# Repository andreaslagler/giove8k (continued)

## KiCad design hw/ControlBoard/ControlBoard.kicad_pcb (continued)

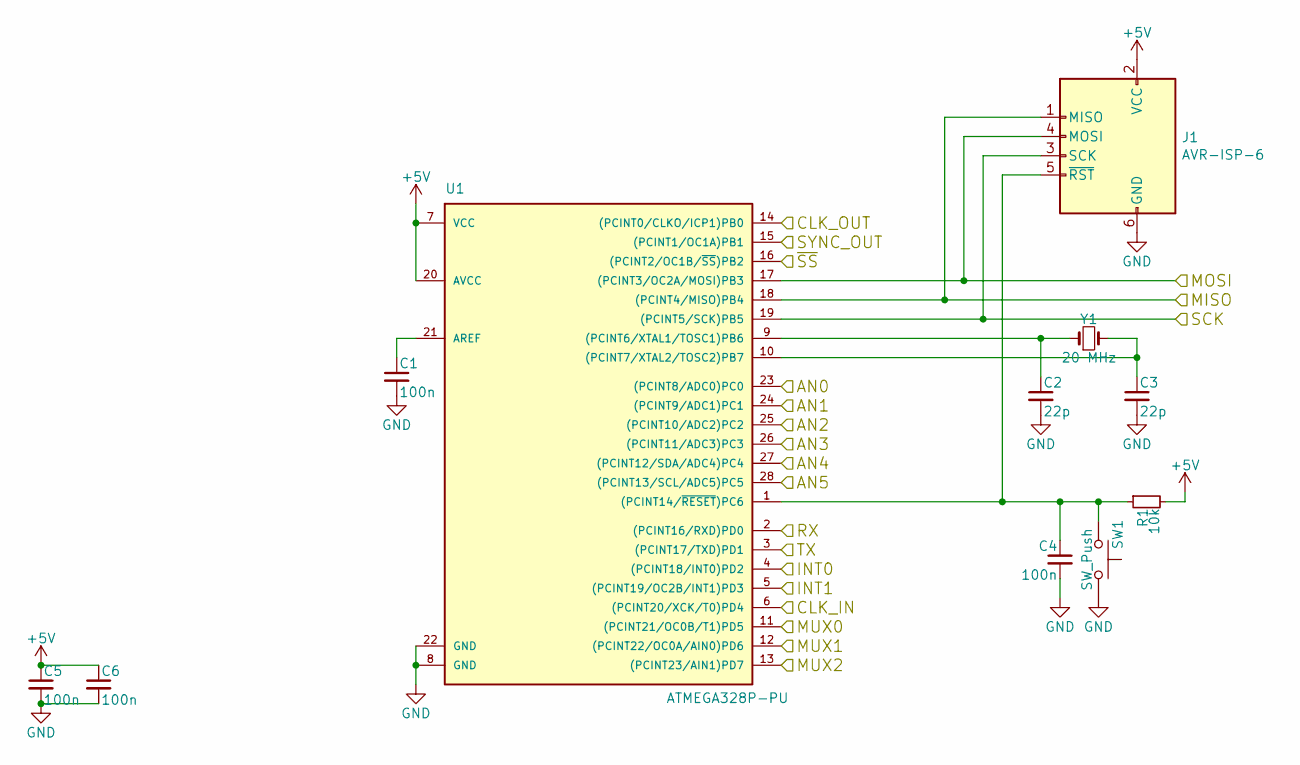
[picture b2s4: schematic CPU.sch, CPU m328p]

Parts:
C1, C4, C5, C6: 100n; C_Disc_D5.0mm_W2.5mm_P5.00mm
C2, C3: 22p; C_Disc_D3.0mm_W1.6mm_P2.50mm
J1: AVR-ISP-6; IDC-Header_2x03_P2.54mm_Vertical
R1: 10k; R_Axial_DIN0207_L6.3mm_D2.5mm_P10.16mm_Horizontal
SW1: SW_Push; SW_PUSH_6mm
U1: ATMEGA328P-PU; DIP-28_W7.62mm
Y1: 20 MHz; Crystal_HC49-U_Vertical

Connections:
+5V: C5.1, C6.1, J1.2 (VCC), R1.2, U1.7 (VCC), U1.20 (AVCC); also elsewhere on the board
/Controller/AN0: U1.23 ((PCINT8/ADC0)PC0); also elsewhere on the board
/Controller/AN1: U1.24 ((PCINT9/ADC1)PC1); also elsewhere on the board
/Controller/AN2: U1.25 ((PCINT10/ADC2)PC2); also elsewhere on the board
/Controller/AN3: U1.26 ((PCINT11/ADC3)PC3); also elsewhere on the board
/Controller/AN4: U1.27 ((PCINT12/SDA/ADC4)PC4); also elsewhere on the board
/Controller/CLK_IN: U1.6 ((PCINT20/XCK/T0)PD4); also elsewhere on the board
/Controller/CLK_OUT: U1.14 ((PCINT0/CLKO/ICP1)PB0); also elsewhere on the board
/Controller/INT0: U1.4 ((PCINT18/INT0)PD2); also elsewhere on the board
/Controller/INT1: U1.5 ((PCINT19/OC2B/INT1)PD3); also elsewhere on the board
/Controller/MUX0: U1.11 ((PCINT21/OC0B/T1)PD5); also elsewhere on the board
/Controller/MUX1: U1.12 ((PCINT22/OC0A/AIN0)PD6); also elsewhere on the board
/Controller/MUX2: U1.13 ((PCINT23/AIN1)PD7); also elsewhere on the board
/Controller/Rx: U1.2 ((PCINT16/RXD)PD0); also elsewhere on the board
/Controller/SCK: J1.3 (SCK), U1.19 ((PCINT5/SCK)PB5); also elsewhere on the board
/Controller/SDI: J1.1 (MISO), U1.18 ((PCINT4/MISO)PB4); also elsewhere on the board
/Controller/SDO: J1.4 (MOSI), U1.17 ((PCINT3/OC2A/MOSI)PB3); also elsewhere on the board
/Controller/SYNC_OUT: U1.15 ((PCINT1/OC1A)PB1); also elsewhere on the board
/Controller/Tx: U1.3 ((PCINT17/TXD)PD1); also elsewhere on the board
/Controller/~SS: U1.16 ((PCINT2/OC1B/~SS~)PB2); also elsewhere on the board
GND: C1.2, C2.2, C3.2, C4.2, C5.2, C6.2, J1.6 (GND), SW1.1, U1.8 (GND), U1.22 (GND); also elsewhere on the board
unnamed: C1.1, U1.21 (AREF)
unnamed: C2.1, U1.9 ((PCINT6/XTAL1/TOSC1)PB6), Y1.1
unnamed: C3.1, U1.10 ((PCINT7/XTAL2/TOSC2)PB7), Y1.2
unnamed: C4.1, J1.5 (~RST), R1.1, SW1.2, U1.1 ((PCINT14/~RESET~)PC6)

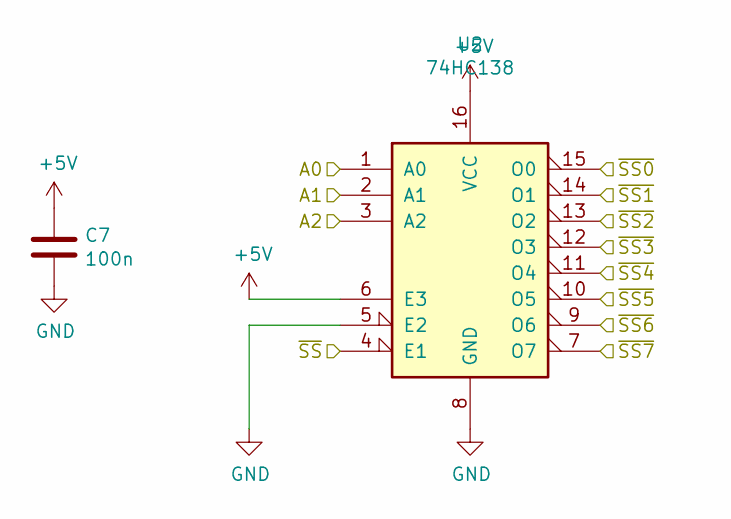
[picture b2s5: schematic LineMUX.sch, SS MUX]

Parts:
C7: 100n; C_Disc_D5.0mm_W2.5mm_P5.00mm
U2: 74HC138; DIP-16_W7.62mm

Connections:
+5V: C7.1, U2.6 (E3), U2.16 (VCC); also elsewhere on the board
/Controller/MUX0: U2.1 (A0); also elsewhere on the board
/Controller/MUX1: U2.2 (A1); also elsewhere on the board
/Controller/MUX2: U2.3 (A2); also elsewhere on the board
/Controller/~SS: U2.4 (E1); also elsewhere on the board
/Controller/~SS0: U2.15 (O0); also elsewhere on the board
/Controller/~SS1: U2.14 (O1); also elsewhere on the board
/Controller/~SS3: U2.12 (O3); also elsewhere on the board
/Controller/~SS4: U2.11 (O4); also elsewhere on the board
/Controller/~SS5: U2.10 (O5); also elsewhere on the board
/Controller/~SS6: U2.9 (O6); also elsewhere on the board
/Controller/~SS7: U2.7 (O7); also elsewhere on the board
/Controller/~SSDSP: U2.13 (O2); also elsewhere on the board
GND: C7.2, U2.5 (E2), U2.8 (GND); also elsewhere on the board

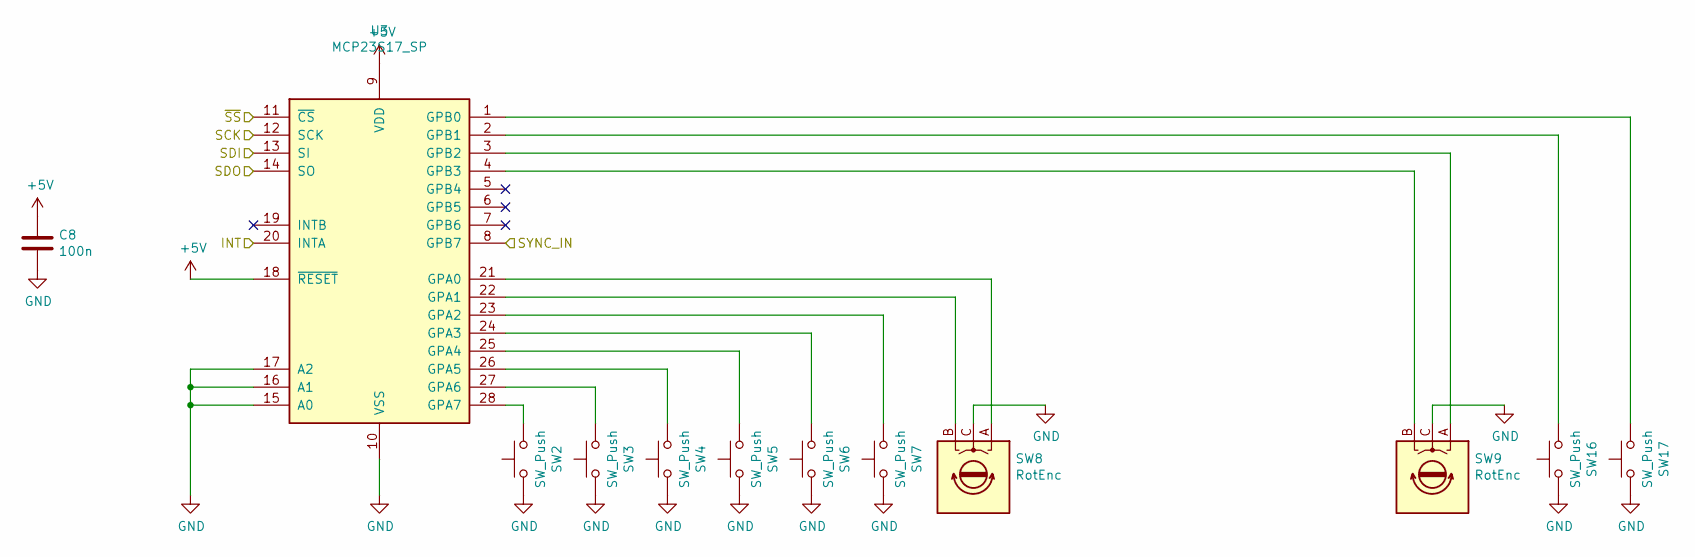
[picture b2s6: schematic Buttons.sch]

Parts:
C8: 100n; C_Disc_D5.0mm_W2.5mm_P5.00mm
SW2, SW3, SW4, SW5, SW6, SW7, SW16, SW17: SW_Push; SW_PUSH-12mm
SW8, SW9: RotEnc; RotaryEncoder_Alps_EC12E_Vertical_H20mm_CircularMountingHol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
U3: MCP23S17_SP; DIP-28_W7.62mm

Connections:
+5V: C8.1, U3.9 (VDD), U3.18 (~RESET~); also elsewhere on the board
/Controller/INT1: U3.20 (INTA); also elsewhere on the board
/Controller/SCK: U3.12 (SCK); also elsewhere on the board
/Controller/SDI: U3.14 (SO); also elsewhere on the board
/Controller/SDO: U3.13 (SI); also elsewhere on the board
/Controller/SYNC_IN: U3.8 (GPB7); also elsewhere on the board
/Controller/~SS1: U3.11 (~CS~); also elsewhere on the board
GND: C8.2, SW2.1, SW3.1, SW4.1, SW5.1, SW6.1, SW7.1, SW8.C, SW9.C, SW16.1, SW17.1, U3.10 (VSS), U3.15 (A0), U3.16 (A1), U3.17 (A2); also elsewhere on the board
unnamed: SW2.2, U3.28 (GPA7)
unnamed: SW3.2, U3.27 (GPA6)
unnamed: SW4.2, U3.26 (GPA5)
unnamed: SW5.2, U3.25 (GPA4)
unnamed: SW6.2, U3.24 (GPA3)
unnamed: SW7.2, U3.23 (GPA2)
unnamed: SW8.A, U3.21 (GPA0)
unnamed: SW8.B, U3.22 (GPA1)
unnamed: SW9.A, U3.3 (GPB2)
unnamed: SW9.B, U3.4 (GPB3)
unnamed: SW16.2, U3.2 (GPB1)
unnamed: SW17.2, U3.1 (GPB0)

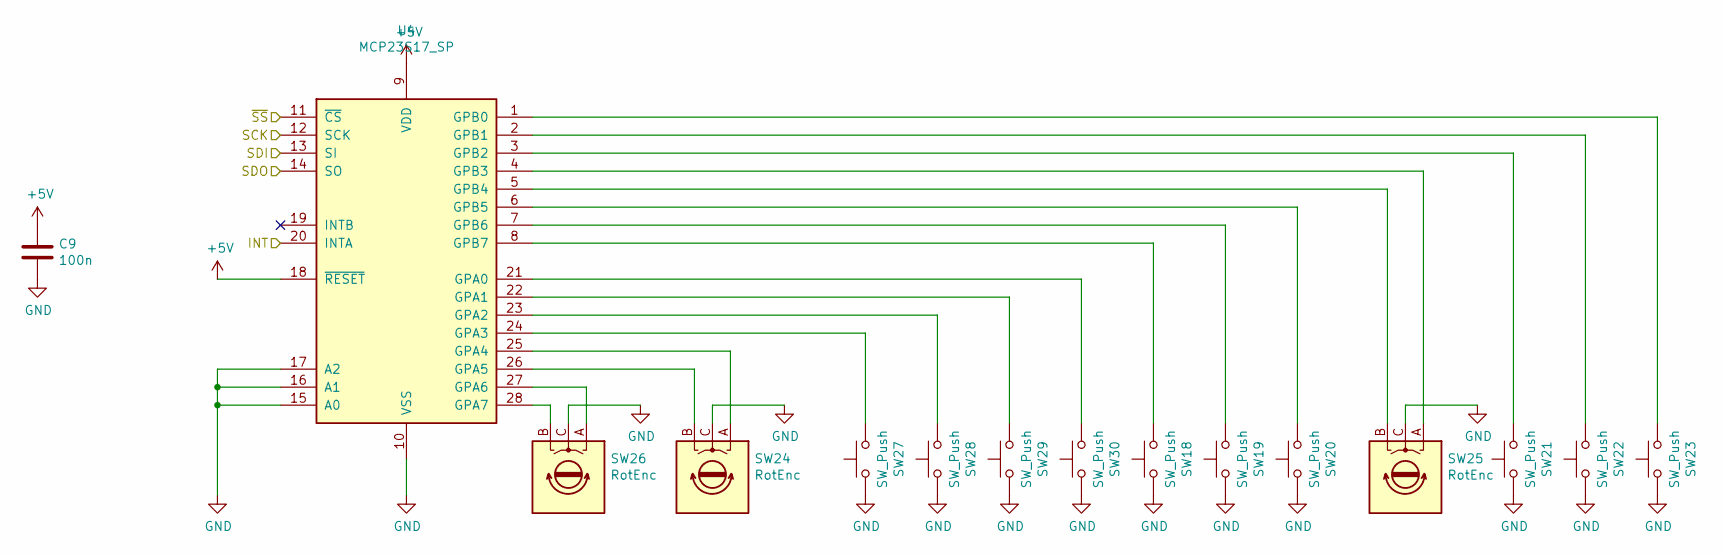
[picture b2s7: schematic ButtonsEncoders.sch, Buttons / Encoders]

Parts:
C9: 100n; C_Disc_D5.0mm_W2.5mm_P5.00mm
SW18, SW19, SW20, SW21, SW22, SW23, SW27, SW28, SW29, SW30: SW_Push; SW_PUSH-12mm
SW24, SW25, SW26: RotEnc; RotaryEncoder_Alps_EC12E_Vertical_H20mm_CircularMountingHol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
U4: MCP23S17_SP; DIP-28_W7.62mm

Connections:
+5V: C9.1, U4.9 (VDD), U4.18 (~RESET~); also elsewhere on the board
/Controller/INT0: U4.20 (INTA); also elsewhere on the board
/Controller/SCK: U4.12 (SCK); also elsewhere on the board
/Controller/SDI: U4.14 (SO); also elsewhere on the board
/Controller/SDO: U4.13 (SI); also elsewhere on the board
/Controller/~SS7: U4.11 (~CS~); also elsewhere on the board
GND: C9.2, SW18.1, SW19.1, SW20.1, SW21.1, SW22.1, SW23.1, SW24.C, SW25.C, SW26.C, SW27.1, SW28.1, SW29.1, SW30.1, U4.10 (VSS), U4.15 (A0), U4.16 (A1), U4.17 (A2); also elsewhere on the board
unnamed: SW18.2, U4.8 (GPB7)
unnamed: SW19.2, U4.7 (GPB6)
unnamed: SW20.2, U4.6 (GPB5)
unnamed: SW21.2, U4.3 (GPB2)
unnamed: SW22.2, U4.2 (GPB1)
unnamed: SW23.2, U4.1 (GPB0)
unnamed: SW24.A, U4.25 (GPA4)
unnamed: SW24.B, U4.26 (GPA5)
unnamed: SW25.A, U4.4 (GPB3)
unnamed: SW25.B, U4.5 (GPB4)
unnamed: SW26.A, U4.27 (GPA6)
unnamed: SW26.B, U4.28 (GPA7)
unnamed: SW27.2, U4.24 (GPA3)
unnamed: SW28.2, U4.23 (GPA2)
unnamed: SW29.2, U4.22 (GPA1)
unnamed: SW30.2, U4.21 (GPA0)

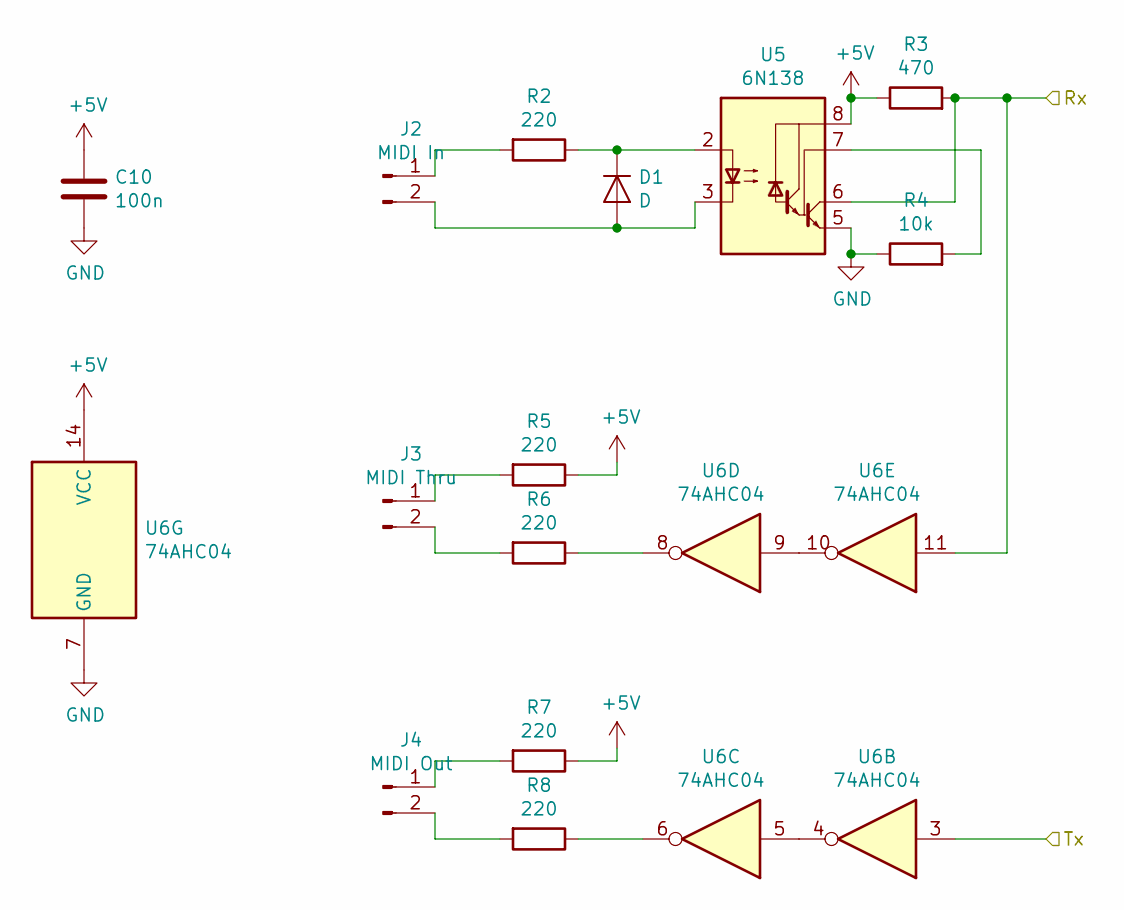
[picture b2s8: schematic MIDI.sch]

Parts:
C10: 100n; C_Disc_D5.0mm_W2.5mm_P5.00mm
D1: D; D_A-405_P10.16mm_Horizontal
J2: MIDI In; Molex_KK-254_AE-6410-02A_1x02_P2.54mm_Vertical
J3: MIDI Thru; Molex_KK-254_AE-6410-02A_1x02_P2.54mm_Vertical
J4: MIDI Out; Molex_KK-254_AE-6410-02A_1x02_P2.54mm_Vertical
R2, R5, R6, R7, R8: 220; R_Axial_DIN0207_L6.3mm_D2.5mm_P10.16mm_Horizontal
R3: 470; R_Axial_DIN0207_L6.3mm_D2.5mm_P10.16mm_Horizontal
R4: 10k; R_Axial_DIN0207_L6.3mm_D2.5mm_P10.16mm_Horizontal
U5: 6N138; DIP-8_W7.62mm
U6: 74AHC04; DIP-14_W7.62mm

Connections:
+5V: C10.1, R3.1, R5.1, R7.1, U5.8 (VCC), U6.14 (VCC); also elsewhere on the board
/Controller/Rx: R3.2, U5.6 (VO2), U6.11; also elsewhere on the board
/Controller/Tx: U6.3; also elsewhere on the board
GND: C10.2, R4.1, U5.5 (GND), U6.7 (GND); also elsewhere on the board
unnamed: D1.1 (K), R2.1, U5.2 (C1)
unnamed: D1.2 (A), J2.2, U5.3 (C2)
unnamed: J2.1, R2.2
unnamed: J3.1, R5.2
unnamed: J3.2, R6.2
unnamed: J4.1, R7.2
unnamed: J4.2, R8.2
unnamed: R4.2, U5.7 (VO1)
unnamed: R6.1, U6.8
unnamed: R8.1, U6.6
unnamed: U6.4, U6.5
unnamed: U6.9, U6.10

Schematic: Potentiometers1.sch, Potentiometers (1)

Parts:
C11: 100n; C_Disc_D5.0mm_W2.5mm_P5.00mm
RV1, RV2, RV3, RV4, RV5, RV6, RV7, RV8: 10kB; Potentiometer_Alpha_RD901F-40-00D_Single_Vertical_CircularH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
U7: 4051; DIP-16_W7.62mm

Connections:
+5V: C11.1, RV1.3, RV2.3, RV3.3, RV4.3, RV5.3, RV6.3, RV7.3, RV8.3, U7.16 (VDD); also elsewhere on the board
/Controller/AN2: U7.3 (X); also elsewhere on the board
/Controller/MUX0: U7.11 (A); also elsewhere on the board
/Controller/MUX1: U7.10 (B); also elsewhere on the board
/Controller/MUX2: U7.9 (C); also elsewhere on the board
GND: C11.2, RV1.1, RV2.1, RV3.1, RV4.1, RV5.1, RV6.1, RV7.1, RV8.1, U7.6 (Inh), U7.7 (VEE), U7.8 (VSS); also elsewhere on the board
unnamed: RV1.2, U7.4 (X7)
unnamed: RV2.2, U7.2 (X6)
unnamed: RV3.2, U7.5 (X5)
unnamed: RV4.2, U7.1 (X4)
unnamed: RV5.2, U7.12 (X3)
unnamed: RV6.2, U7.15 (X2)
unnamed: RV7.2, U7.14 (X1)
unnamed: RV8.2, U7.13 (X0)

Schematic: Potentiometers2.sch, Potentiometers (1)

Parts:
C12: 100n; C_Disc_D5.0mm_W2.5mm_P5.00mm
RV9, RV10, RV11, RV12, RV13, RV14, RV15, RV16: 10kB; Potentiometer_Alpha_RD901F-40-00D_Single_Vertical_CircularH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
U8: 4051; DIP-16_W7.62mm

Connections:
+5V: C12.1, RV9.3, RV10.3, RV11.3, RV12.3, RV13.3, RV14.3, RV15.3, RV16.3, U8.16 (VDD); also elsewhere on the board
/Controller/AN0: U8.3 (X); also elsewhere on the board
/Controller/MUX0: U8.11 (A); also elsewhere on the board
/Controller/MUX1: U8.10 (B); also elsewhere on the board
/Controller/MUX2: U8.9 (C); also elsewhere on the board
GND: C12.2, RV9.1, RV10.1, RV11.1, RV12.1, RV13.1, RV14.1, RV15.1, RV16.1, U8.6 (Inh), U8.7 (VEE), U8.8 (VSS); also elsewhere on the board
unnamed: RV9.2, U8.4 (X7)
unnamed: RV10.2, U8.2 (X6)
unnamed: RV11.2, U8.5 (X5)
unnamed: RV12.2, U8.1 (X4)
unnamed: RV13.2, U8.12 (X3)
unnamed: RV14.2, U8.15 (X2)
unnamed: RV15.2, U8.14 (X1)
unnamed: RV16.2, U8.13 (X0)

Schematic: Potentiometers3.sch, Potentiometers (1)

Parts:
C13: 100n; C_Disc_D5.0mm_W2.5mm_P5.00mm
RV17, RV18, RV19, RV20, RV21, RV22, RV23, RV24: 10kB; Potentiometer_Alpha_RD901F-40-00D_Single_Vertical_CircularH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
U9: 4051; DIP-16_W7.62mm

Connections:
+5V: C13.1, RV17.3, RV18.3, RV19.3, RV20.3, RV21.3, RV22.3, RV23.3, RV24.3, U9.16 (VDD); also elsewhere on the board
/Controller/AN4: U9.3 (X); also elsewhere on the board
/Controller/MUX0: U9.11 (A); also elsewhere on the board
/Controller/MUX1: U9.10 (B); also elsewhere on the board
/Controller/MUX2: U9.9 (C); also elsewhere on the board
GND: C13.2, RV17.1, RV18.1, RV19.1, RV20.1, RV21.1, RV22.1, RV23.1, RV24.1, U9.6 (Inh), U9.7 (VEE), U9.8 (VSS); also elsewhere on the board
unnamed: RV17.2, U9.4 (X7)
unnamed: RV18.2, U9.2 (X6)
unnamed: RV19.2, U9.5 (X5)
unnamed: RV20.2, U9.1 (X4)
unnamed: RV21.2, U9.12 (X3)
unnamed: RV22.2, U9.15 (X2)
unnamed: RV23.2, U9.14 (X1)
unnamed: RV24.2, U9.13 (X0)

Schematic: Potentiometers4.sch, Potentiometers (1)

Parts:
C14: 100n; C_Disc_D5.0mm_W2.5mm_P5.00mm
RV25, RV26, RV27, RV28, RV30, RV31, RV32: 10kB; Potentiometer_Alpha_RD901F-40-00D_Single_Vertical_CircularH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
U10: 4051; DIP-16_W7.62mm

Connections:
+5V: C14.1, RV25.3, RV26.3, RV27.3, RV28.3, RV30.3, RV31.3, RV32.3, U10.16 (VDD); also elsewhere on the board
/Controller/AN3: U10.3 (X); also elsewhere on the board
/Controller/MUX0: U10.11 (A); also elsewhere on the board
/Controller/MUX1: U10.10 (B); also elsewhere on the board
/Controller/MUX2: U10.9 (C); also elsewhere on the board
GND: C14.2, RV25.1, RV26.1, RV27.1, RV28.1, RV30.1, RV31.1, RV32.1, U10.6 (Inh), U10.7 (VEE), U10.8 (VSS); also elsewhere on the board
unnamed: RV25.2, U10.4 (X7)
unnamed: RV26.2, U10.2 (X6)
unnamed: RV27.2, U10.5 (X5)
unnamed: RV28.2, U10.1 (X4)
unnamed: RV30.2, U10.15 (X2)
unnamed: RV31.2, U10.14 (X1)
unnamed: RV32.2, U10.13 (X0)

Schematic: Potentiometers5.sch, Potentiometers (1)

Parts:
C15: 100n; C_Disc_D5.0mm_W2.5mm_P5.00mm
RV33, RV34, RV35, RV36, RV37, RV40, RV42: 10kB; Potentiometer_Alpha_RD901F-40-00D_Single_Vertical_CircularH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
U11: 4051; DIP-16_W7.62mm

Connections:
+5V: C15.1, RV33.3, RV34.3, RV35.3, RV36.3, RV37.3, RV40.3, RV42.3, U11.16 (VDD); also elsewhere on the board
/Controller/AN1: U11.3 (X); also elsewhere on the board
/Controller/MUX0: U11.11 (A); also elsewhere on the board
/Controller/MUX1: U11.10 (B); also elsewhere on the board
/Controller/MUX2: U11.9 (C); also elsewhere on the board
GND: C15.2, RV33.1, RV34.1, RV35.1, RV36.1, RV37.1, RV40.1, RV42.1, U11.6 (Inh), U11.7 (VEE), U11.8 (VSS); also elsewhere on the board
unnamed: RV33.2, U11.4 (X7)
unnamed: RV34.2, U11.2 (X6)
unnamed: RV35.2, U11.5 (X5)
unnamed: RV36.2, U11.1 (X4)
unnamed: RV37.2, U11.12 (X3)
unnamed: RV40.2, U11.14 (X1)
unnamed: RV42.2, U11.13 (X0)

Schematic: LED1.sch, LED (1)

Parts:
C16: 100n; C_Disc_D5.0mm_W2.5mm_P5.00mm
D2, D3, D4, D5, D6, D7, D8, D9: LED; LED_D3.0mm
R9, R10, R11, R12, R13, R14, R15, R16: 1k5; R_Axial_DIN0207_L6.3mm_D2.5mm_P10.16mm_Horizontal
U12: 74HC595; DIP-16_W7.62mm

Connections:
+5V: C16.1, U12.10 (~SRCLR), U12.16 (VCC); also elsewhere on the board
/Controller/LED (1)/SDI: U12.14 (SER); also elsewhere on the board
/Controller/LED (3)/SDI: U12.9 (QH'); also elsewhere on the board
/Controller/SCK: U12.11 (SRCLK); also elsewhere on the board
/Controller/~SS0: U12.12 (RCLK); also elsewhere on the board
GND: C16.2, D2.1 (K), D3.1 (K), D4.1 (K), D5.1 (K), D6.1 (K), D7.1 (K), D8.1 (K), D9.1 (K), U12.8 (GND), U12.13 (~OE); also elsewhere on the board
unnamed: D2.2 (A), R9.2
unnamed: D3.2 (A), R10.2
unnamed: D4.2 (A), R11.2
unnamed: D5.2 (A), R12.2
unnamed: D6.2 (A), R13.2
unnamed: D7.2 (A), R14.2
unnamed: D8.2 (A), R15.2
unnamed: D9.2 (A), R16.2
unnamed: R9.1, U12.7 (QH)
unnamed: R10.1, U12.6 (QG)
unnamed: R11.1, U12.5 (QF)
unnamed: R12.1, U12.4 (QE)
unnamed: R13.1, U12.3 (QD)
unnamed: R14.1, U12.2 (QC)
unnamed: R15.1, U12.1 (QB)
unnamed: R16.1, U12.15 (QA)

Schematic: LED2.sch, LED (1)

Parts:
C17: 100n; C_Disc_D5.0mm_W2.5mm_P5.00mm
D10, D11, D12, D13, D14, D15: LED; LED_D3.0mm
R17, R18, R19, R20, R21, R22: 1k5; R_Axial_DIN0207_L6.3mm_D2.5mm_P10.16mm_Horizontal
U13: 74HC595; DIP-16_W7.62mm

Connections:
+5V: C17.1, U13.10 (~SRCLR), U13.16 (VCC); also elsewhere on the board
/Controller/LED (1)/SDI: U13.9 (QH'); also elsewhere on the board
/Controller/LED (2)/SDI: U13.14 (SER); also elsewhere on the board
/Controller/SCK: U13.11 (SRCLK); also elsewhere on the board
/Controller/~SS0: U13.12 (RCLK); also elsewhere on the board
GND: C17.2, D10.1 (K), D11.1 (K), D12.1 (K), D13.1 (K), D14.1 (K), D15.1 (K), U13.8 (GND), U13.13 (~OE); also elsewhere on the board
unnamed: D10.2 (A), R17.2
unnamed: D11.2 (A), R18.2
unnamed: D12.2 (A), R19.2
unnamed: D13.2 (A), R20.2
unnamed: D14.2 (A), R21.2
unnamed: D15.2 (A), R22.2
unnamed: R17.1, U13.7 (QH)
unnamed: R18.1, U13.6 (QG)
unnamed: R19.1, U13.5 (QF)
unnamed: R20.1, U13.4 (QE)
unnamed: R21.1, U13.3 (QD)
unnamed: R22.1, U13.2 (QC)

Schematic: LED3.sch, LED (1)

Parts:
C18: 100n; C_Disc_D5.0mm_W2.5mm_P5.00mm
D18, D19, D20, D21, D22, D23, D24, D25: LED; LED_D3.0mm
R25, R26, R27, R28, R29, R30, R31, R32: 1k5; R_Axial_DIN0207_L6.3mm_D2.5mm_P10.16mm_Horizontal
U14: 74HC595; DIP-16_W7.62mm

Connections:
+5V: C18.1, U14.10 (~SRCLR), U14.16 (VCC); also elsewhere on the board
/Controller/LED (3)/SDI: U14.14 (SER); also elsewhere on the board
/Controller/SCK: U14.11 (SRCLK); also elsewhere on the board
/Controller/~SS0: U14.12 (RCLK); also elsewhere on the board
GND: C18.2, D18.1 (K), D19.1 (K), D20.1 (K), D21.1 (K), D22.1 (K), D23.1 (K), D24.1 (K), D25.1 (K), U14.8 (GND), U14.13 (~OE); also elsewhere on the board
unnamed: D18.2 (A), R25.2
unnamed: D19.2 (A), R26.2
unnamed: D20.2 (A), R27.2
unnamed: D21.2 (A), R28.2
unnamed: D22.2 (A), R29.2
unnamed: D23.2 (A), R30.2
unnamed: D24.2 (A), R31.2
unnamed: D25.2 (A), R32.2
unnamed: R25.1, U14.7 (QH)
unnamed: R26.1, U14.6 (QG)
unnamed: R27.1, U14.5 (QF)
unnamed: R28.1, U14.4 (QE)
unnamed: R29.1, U14.3 (QD)
unnamed: R30.1, U14.2 (QC)
unnamed: R31.1, U14.1 (QB)
unnamed: R32.1, U14.15 (QA)

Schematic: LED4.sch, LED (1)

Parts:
C19: 100n; C_Disc_D5.0mm_W2.5mm_P5.00mm
D26, D27, D28, D29, D30, D31, D32, D33: LED; LED_D3.0mm
R33, R34, R35, R36, R37, R38, R39, R40: 1k5; R_Axial_DIN0207_L6.3mm_D2.5mm_P10.16mm_Horizontal
U15: 74HC595; DIP-16_W7.62mm

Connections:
+5V: C19.1, U15.10 (~SRCLR), U15.16 (VCC); also elsewhere on the board
/Controller/LED (2)/SDI: U15.9 (QH'); also elsewhere on the board
/Controller/LED (4)/SDI: U15.14 (SER); also elsewhere on the board
/Controller/SCK: U15.11 (SRCLK); also elsewhere on the board
/Controller/~SS0: U15.12 (RCLK); also elsewhere on the board
GND: C19.2, D26.1 (K), D27.1 (K), D28.1 (K), D29.1 (K), D30.1 (K), D31.1 (K), D32.1 (K), D33.1 (K), U15.8 (GND), U15.13 (~OE); also elsewhere on the board
unnamed: D26.2 (A), R33.2
unnamed: D27.2 (A), R34.2
unnamed: D28.2 (A), R35.2
unnamed: D29.2 (A), R36.2
unnamed: D30.2 (A), R37.2
unnamed: D31.2 (A), R38.2
unnamed: D32.2 (A), R39.2
unnamed: D33.2 (A), R40.2
unnamed: R33.1, U15.7 (QH)
unnamed: R34.1, U15.6 (QG)
unnamed: R35.1, U15.5 (QF)
unnamed: R36.1, U15.4 (QE)
unnamed: R37.1, U15.3 (QD)
unnamed: R38.1, U15.2 (QC)
unnamed: R39.1, U15.1 (QB)
unnamed: R40.1, U15.15 (QA)

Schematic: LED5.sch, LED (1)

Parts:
C20: 100n; C_Disc_D5.0mm_W2.5mm_P5.00mm
D34, D35, D36, D37, D38, D39, D40, D41: LED; LED_D3.0mm
R41, R42, R43, R44, R45, R46, R47, R48: 1k5; R_Axial_DIN0207_L6.3mm_D2.5mm_P10.16mm_Horizontal
U16: 74HC595; DIP-16_W7.62mm

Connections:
+5V: C20.1, U16.10 (~SRCLR), U16.16 (VCC); also elsewhere on the board
/Controller/LED (4)/SDI: U16.9 (QH'); also elsewhere on the board
/Controller/LED (5)/SDI: U16.14 (SER); also elsewhere on the board
/Controller/SCK: U16.11 (SRCLK); also elsewhere on the board
/Controller/~SS0: U16.12 (RCLK); also elsewhere on the board
GND: C20.2, D34.1 (K), D35.1 (K), D36.1 (K), D37.1 (K), D38.1 (K), D39.1 (K), D40.1 (K), D41.1 (K), U16.8 (GND), U16.13 (~OE); also elsewhere on the board
unnamed: D34.2 (A), R41.2
unnamed: D35.2 (A), R42.2
unnamed: D36.2 (A), R43.2
unnamed: D37.2 (A), R44.2
unnamed: D38.2 (A), R45.2
unnamed: D39.2 (A), R46.2
unnamed: D40.2 (A), R47.2
unnamed: D41.2 (A), R48.2
unnamed: R41.1, U16.7 (QH)
unnamed: R42.1, U16.6 (QG)
unnamed: R43.1, U16.5 (QF)
unnamed: R44.1, U16.4 (QE)
unnamed: R45.1, U16.3 (QD)
unnamed: R46.1, U16.2 (QC)
unnamed: R47.1, U16.1 (QB)
unnamed: R48.1, U16.15 (QA)

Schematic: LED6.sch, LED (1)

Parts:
C21: 100n; C_Disc_D5.0mm_W2.5mm_P5.00mm
D42, D43, D44, D45, D46, D47, D48, D49: LED; LED_D3.0mm
R49, R50, R51, R52, R53, R54, R55, R56: 1k5; R_Axial_DIN0207_L6.3mm_D2.5mm_P10.16mm_Horizontal
U17: 74HC595; DIP-16_W7.62mm

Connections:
+5V: C21.1, U17.10 (~SRCLR), U17.16 (VCC); also elsewhere on the board
/Controller/LED (5)/SDI: U17.9 (QH'); also elsewhere on the board
/Controller/SCK: U17.11 (SRCLK); also elsewhere on the board
/Controller/SDO: U17.14 (SER); also elsewhere on the board
/Controller/~SS0: U17.12 (RCLK); also elsewhere on the board
GND: C21.2, D42.1 (K), D43.1 (K), D44.1 (K), D45.1 (K), D46.1 (K), D47.1 (K), D48.1 (K), D49.1 (K), U17.8 (GND), U17.13 (~OE); also elsewhere on the board
unnamed: D42.2 (A), R49.2
unnamed: D43.2 (A), R50.2
unnamed: D44.2 (A), R51.2
unnamed: D45.2 (A), R52.2
unnamed: D46.2 (A), R53.2
unnamed: D47.2 (A), R54.2
unnamed: D48.2 (A), R55.2
unnamed: D49.2 (A), R56.2
unnamed: R49.1, U17.7 (QH)
unnamed: R50.1, U17.6 (QG)
unnamed: R51.1, U17.5 (QF)
unnamed: R52.1, U17.4 (QE)
unnamed: R53.1, U17.3 (QD)
unnamed: R54.1, U17.2 (QC)
unnamed: R55.1, U17.1 (QB)
unnamed: R56.1, U17.15 (QA)

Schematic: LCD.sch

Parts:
C22: 100n; C_Disc_D5.0mm_W2.5mm_P5.00mm
DS1: WC1602A
Q1: 2N3904; TO-92
R57: 10k; R_Axial_DIN0207_L6.3mm_D2.5mm_P10.16mm_Horizontal
R58: 100k; R_Axial_DIN0207_L6.3mm_D2.5mm_P10.16mm_Horizontal
R59: 100; R_Axial_DIN0207_L6.3mm_D2.5mm_P10.16mm_Horizontal
RV41: 10k; Potentiometer_Piher_PT-6-V_Vertical
U18: 74HC595; DIP-16_W7.62mm

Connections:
+5V: C22.1, DS1.2 (VDD), DS1.15 (LED(+)), R57.1, RV41.3, U18.10 (~SRCLR), U18.16 (VCC); also elsewhere on the board
/Controller/SCK: U18.11 (SRCLK); also elsewhere on the board
/Controller/SDO: U18.14 (SER); also elsewhere on the board
/Controller/~SS3: R58.2, U18.12 (RCLK); also elsewhere on the board
GND: C22.2, DS1.1 (VSS), DS1.5 (R/W), Q1.1 (E), R59.2, RV41.1, U18.8 (GND), U18.13 (~OE); also elsewhere on the board
unnamed: DS1.3 (VO), RV41.2
unnamed: DS1.4 (RS), U18.2 (QC)
unnamed: DS1.6 (E), Q1.3 (C), R57.2
unnamed: DS1.11 (D4), U18.4 (QE)
unnamed: DS1.12 (D5), U18.5 (QF)
unnamed: DS1.13 (D6), U18.6 (QG)
unnamed: DS1.14 (D7), U18.7 (QH)
unnamed: DS1.16 (LED(-)), R59.1
unnamed: Q1.2 (B), R58.1

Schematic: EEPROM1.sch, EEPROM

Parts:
C23: 100n; C_Disc_D5.0mm_W2.5mm_P5.00mm
U19: 25LC512; DIP-8_W7.62mm

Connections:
+5V: C23.1, U19.3 (~WP), U19.7 (~HOLD), U19.8 (VCC); also elsewhere on the board
/Controller/SCK: U19.6 (SCK); also elsewhere on the board
/Controller/SDI: U19.2 (MISO); also elsewhere on the board
/Controller/SDO: U19.5 (MOSI); also elsewhere on the board
/Controller/~SS4: U19.1 (~CS); also elsewhere on the board
GND: C23.2, U19.4 (GND); also elsewhere on the board

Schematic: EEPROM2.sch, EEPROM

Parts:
C28: 100n; C_Disc_D5.0mm_W2.5mm_P5.00mm
U22: 25LC512; DIP-8_W7.62mm

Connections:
+5V: C28.1, U22.3 (~WP), U22.7 (~HOLD), U22.8 (VCC); also elsewhere on the board
/Controller/SCK: U22.6 (SCK); also elsewhere on the board
/Controller/SDI: U22.2 (MISO); also elsewhere on the board
/Controller/SDO: U22.5 (MOSI); also elsewhere on the board
/Controller/~SS5: U22.1 (~CS); also elsewhere on the board
GND: C28.2, U22.4 (GND); also elsewhere on the board

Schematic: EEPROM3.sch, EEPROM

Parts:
C29: 100n; C_Disc_D5.0mm_W2.5mm_P5.00mm
U23: 25LC512; DIP-8_W7.62mm

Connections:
+5V: C29.1, U23.3 (~WP), U23.7 (~HOLD), U23.8 (VCC); also elsewhere on the board
/Controller/SCK: U23.6 (SCK); also elsewhere on the board
/Controller/SDI: U23.2 (MISO); also elsewhere on the board
/Controller/SDO: U23.5 (MOSI); also elsewhere on the board
/Controller/~SS6: U23.1 (~CS); also elsewhere on the board
GND: C29.2, U23.4 (GND); also elsewhere on the board

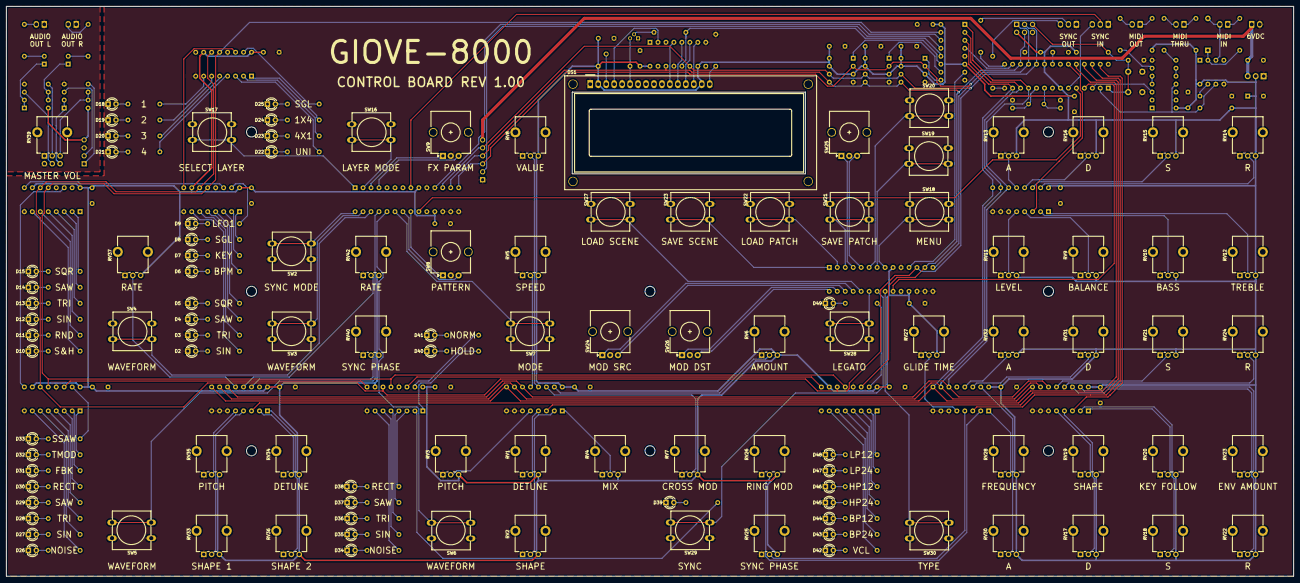
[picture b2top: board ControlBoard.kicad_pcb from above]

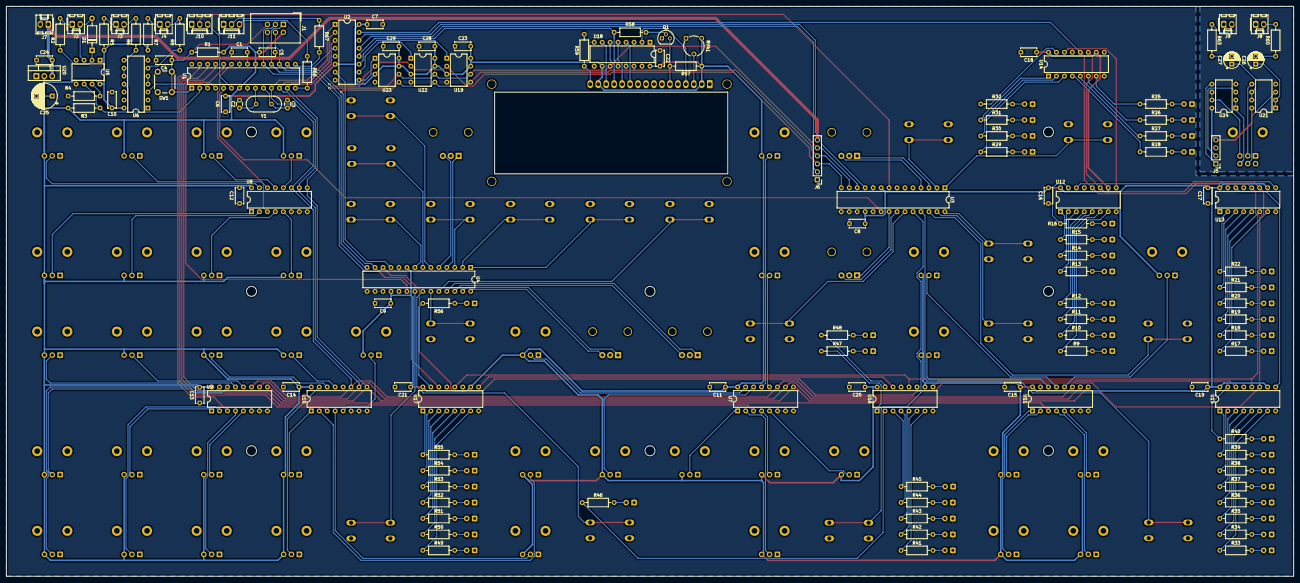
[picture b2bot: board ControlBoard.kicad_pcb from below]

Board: 2 copper layers, 410.2 x 181.6 mm, 239 parts (130 on the bottom side), 235 nets.

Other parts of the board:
J7: 6VDC; Molex_KK-254_AE-6410-02A_1x02_P2.54mm_Vertical

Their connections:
+6V: J7.1; also elsewhere on the board
GND: J7.2; also elsewhere on the board

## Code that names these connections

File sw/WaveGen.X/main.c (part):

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
// FOSC
#pragma config POSCMD = XT              // Primary Oscillator Mode Select bits (XT Crystal Oscillator Mode)
#pragma config OSCIOFNC = OFF           // OSC2 Pin Function bit (OSC2 is clock output)
#pragma config IOL1WAY = ON             // Peripheral pin select configuration (Allow only one reconfiguration)
#pragma config FCKSM = CSECMD           // Clock Switching Mode bits (Clock switching is enabled,Fail-safe Clock Monitor is disabled)

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    ////////////////////////////////////////////////////////////////////////////
    // SPI1 is configured as master with two /SS pins for external SRAM control

    // SCK1 -> Pin 16 - RB7
    TRISBbits.TRISB7 = 0;
    LATBbits.LATB7 = 0;

    // SDO1 -> Pin 17 - RB8
    TRISBbits.TRISB8 = 0;
    LATBbits.LATB8 = 0;

    // SDI1 -> Pin 18 - RB9
    TRISBbits.TRISB9 = 1;
    PORTBbits.RB9 = 0;

    // /SS10 -> Pin 15 - RB6
    TRISBbits.TRISB6 = 0;
    LATBbits.LATB6 = 1;

    // /SS11 -> Pin 22 - RB11
    TRISBbits.TRISB11 = 0;
    LATBbits.LATB11 = 1;

    ////////////////////////////////////////////////////////////////////////////
    // SPI2 is configured as slave

    // /SS2 --> Pin 23 - RB12 / RPI44 (input)
    TRISBbits.TRISB12 = 1;
    RPINR23bits.SS2R = 44;
 
    // SDI2 --> Pin 24 - RB13 / RPI45 (input)
    TRISBbits.TRISB13 = 1;
    RPINR22bits.SDI2R = 45;
 
    // SDO2 --> Pin 25 - RB14 / RPI46 (output) WIRING ERROR
    TRISBbits.TRISB14 = 1;
 
    // SDO2 --> Pin 21 - RB10 / RP42 (output)
    TRISBbits.TRISB10 = 0;
    LATBbits.LATB10 = 0;
    RPOR4bits.RP42R = 0b001000; // SDO2

    // SCK2 --> Pin 26 - RB15 / RPI47 (input)
    TRISBbits.TRISB15 = 1;
    RPINR22bits.SCK2R = 47;

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
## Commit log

2022-02-03 Projects renamed
2024-07-30 Initial version 2.0
